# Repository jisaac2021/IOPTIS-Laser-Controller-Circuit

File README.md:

## IOPTIS NEW GEN Laser Controller Circuit

## **PCB Layout 3D View**

**Front**

**Back**

## **Multi-sheet Schematic Layout**

## **Team**
Julia Isaac - Machine Learning & Software Intern

Loic Billaut - Electrical & Optical Engineering Intern

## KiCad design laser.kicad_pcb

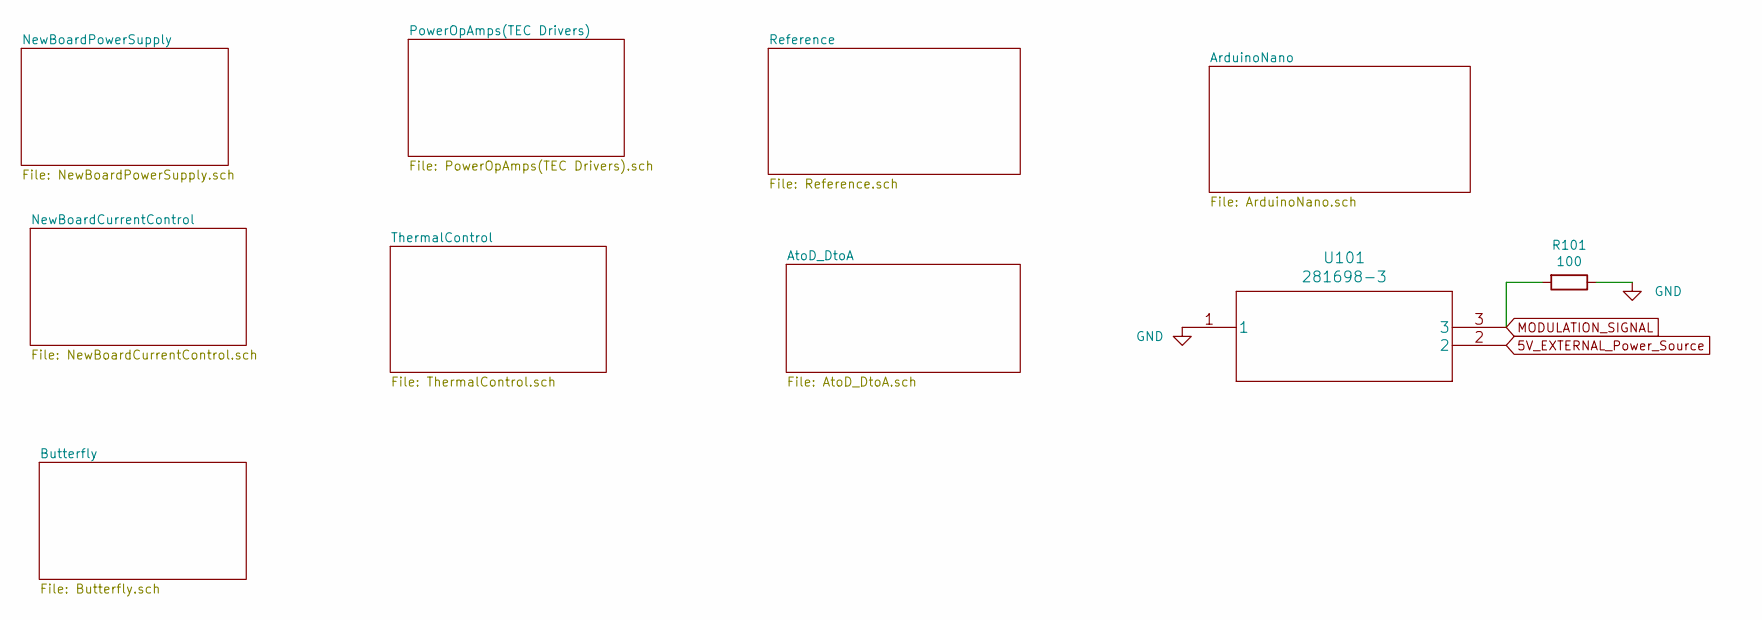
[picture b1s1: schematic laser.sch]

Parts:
R101: 100; R_0402_1005Metric
U101: 281698-3

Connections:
5V_EXTERNAL_Power_Source: U101.2; also elsewhere on the board
GND: R101.1, U101.1; also elsewhere on the board
MODULATION_SIGNAL: R101.2, U101.3; also elsewhere on the board

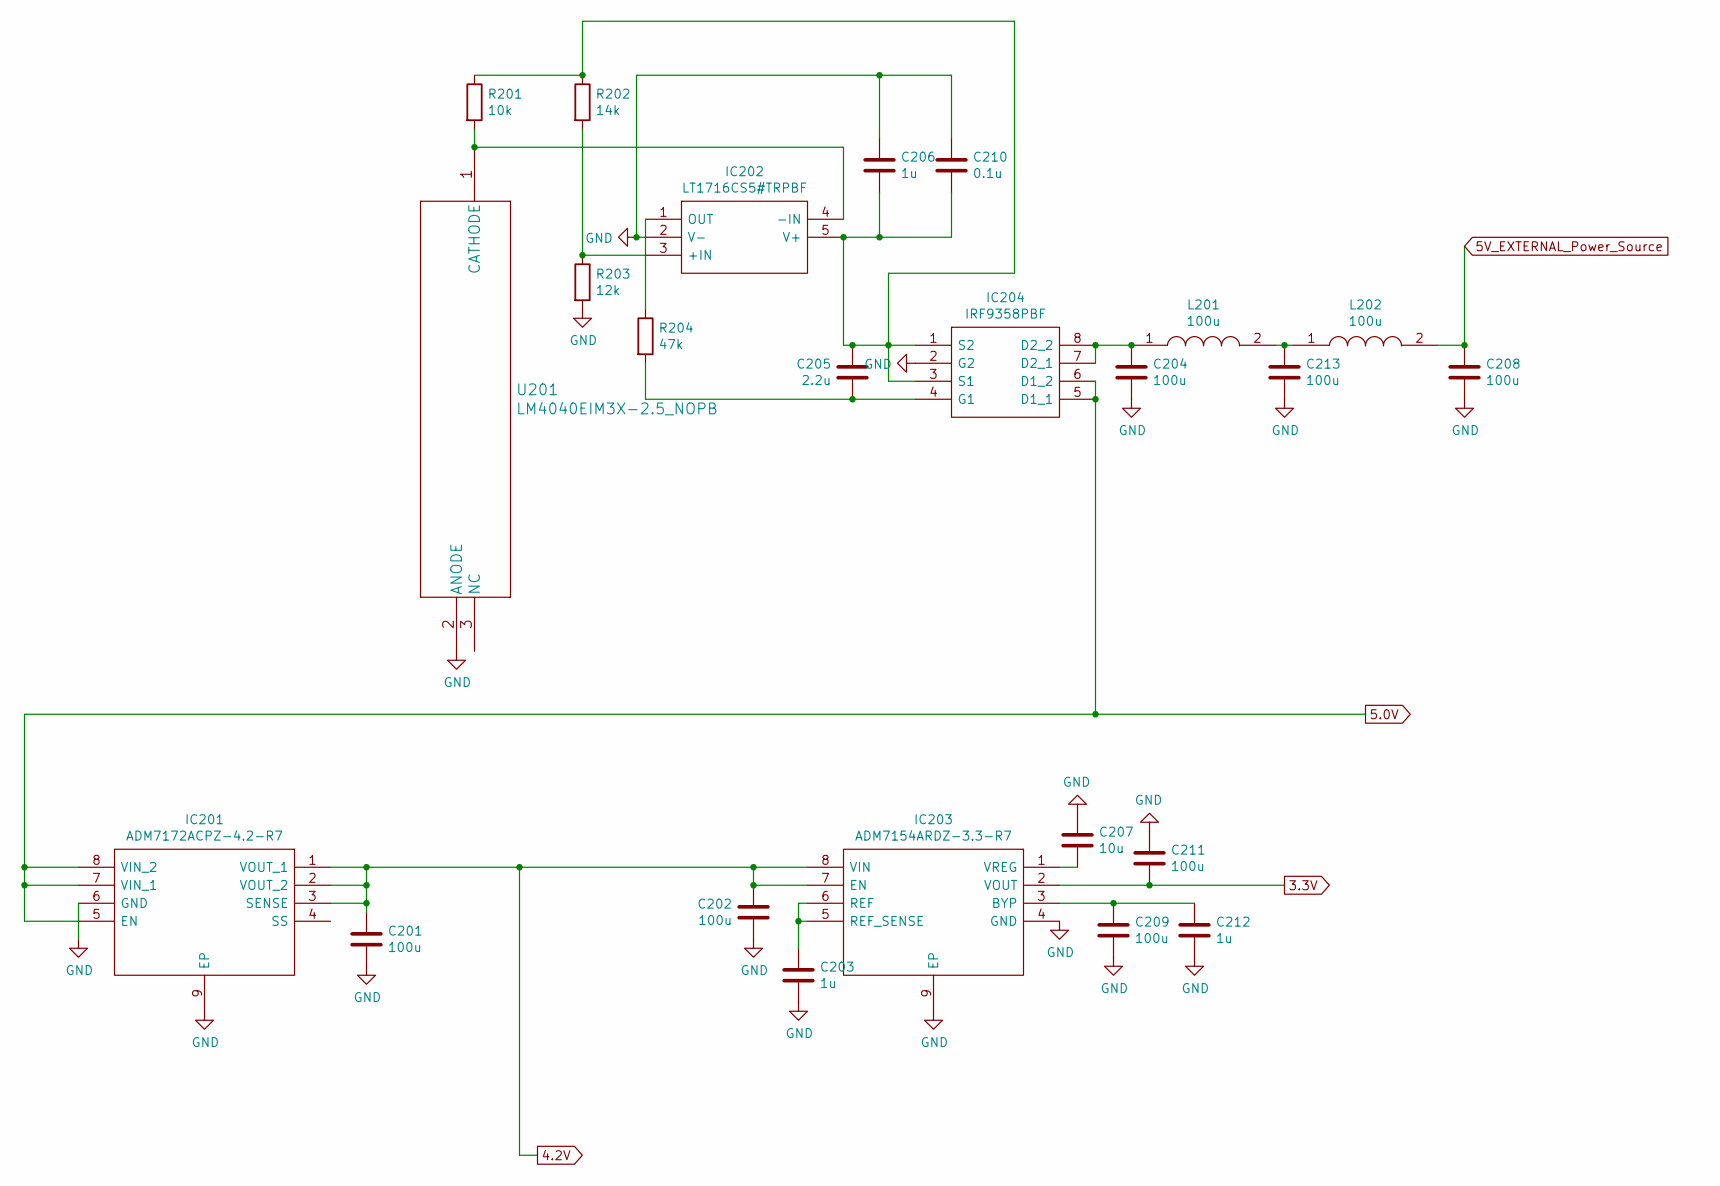
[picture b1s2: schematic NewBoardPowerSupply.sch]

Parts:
C201, C202, C204, C208, C209, C211, C213: 100u; C_1210_3225Metric
C203, C206, C212: 1u; C_0402_1005Metric
C205: 2.2u; C_0402_1005Metric
C207: 10u; C_0402_1005Metric
C210: 0.1u; C_0402_1005Metric
IC201: ADM7172ACPZ-4.2-R7; Manufacturer_Part_Number ADM7172ACPZ-4.2-R7; Mouser Part Number 584-ADM7172ACPZ4.2R7
IC202: LT1716CS5#TRPBF; Manufacturer_Part_Number LT1716CS5#TRPBF; Mouser Part Number 584-LT1716CS5#TRPBF
IC203: ADM7154ARDZ-3.3-R7; ADA4528-2ACPZ-RL; Manufacturer_Part_Number ADM7154ARDZ-3.3-R7; Mouser Part Number 584-ADM7154ARDZ3.3R7
IC204: IRF9358PBF; Manufacturer_Part_Number IRF9358PBF; Mouser Part Number 942-IRF9358PBF
L201, L202: 100u; 7447714220; Manufacturer_Part_Number 7447714101; Mouser Part Number 710-7447714101
R201: 10k; R_0402_1005Metric
R202: 14k; R_0805_2012Metric
R203: 12k; R_0402_1005Metric
R204: 47k; R_0402_1005Metric
U201: LM4040EIM3X-2.5_NOPB; LM4040EIM3X-2.5&slash_NOPB

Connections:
3.3V: C211.2, IC203.2 (VOUT); also elsewhere on the board
4.2V: C201.1, C202.1, IC201.1 (VOUT_1), IC201.2 (VOUT_2), IC201.3 (SENSE), IC203.7 (EN), IC203.8 (VIN); also elsewhere on the board
5.0V: IC201.5 (EN), IC201.7 (VIN_1), IC201.8 (VIN_2), IC204.5 (D1_1), IC204.6 (D1_2); also elsewhere on the board
5V_EXTERNAL_Power_Source: C208.2, L202.2; also elsewhere on the board
GND: C201.2, C202.2, C203.2, C204.1, C206.1, C207.1, C208.1, C209.2, C210.1, C211.1, C212.2, C213.1, IC201.6 (GND), IC201.9 (EP), IC202.2 (V-), IC203.4 (GND), IC203.9 (EP), IC204.2 (G2), R203.2, U201.2 (ANODE); also elsewhere on the board
unnamed: C203.1, IC203.5 (REF_SENSE), IC203.6 (REF)
unnamed: C204.2, IC204.7 (D2_1), IC204.8 (D2_2), L201.1
unnamed: C205.1, C206.2, C210.2, IC202.5 (V+), IC204.1 (S2), IC204.3 (S1), R201.1, R202.1
unnamed: C205.2, IC204.4 (G1), R204.2
unnamed: C207.2, IC203.1 (VREG)
unnamed: C209.1, C212.1, IC203.3 (BYP)
unnamed: C213.2, L201.2, L202.1
unnamed: IC202.1 (OUT), R204.1
unnamed: IC202.3 (+IN), R202.2, R203.1
unnamed: IC202.4 (-IN), R201.2, U201.1 (CATHODE)

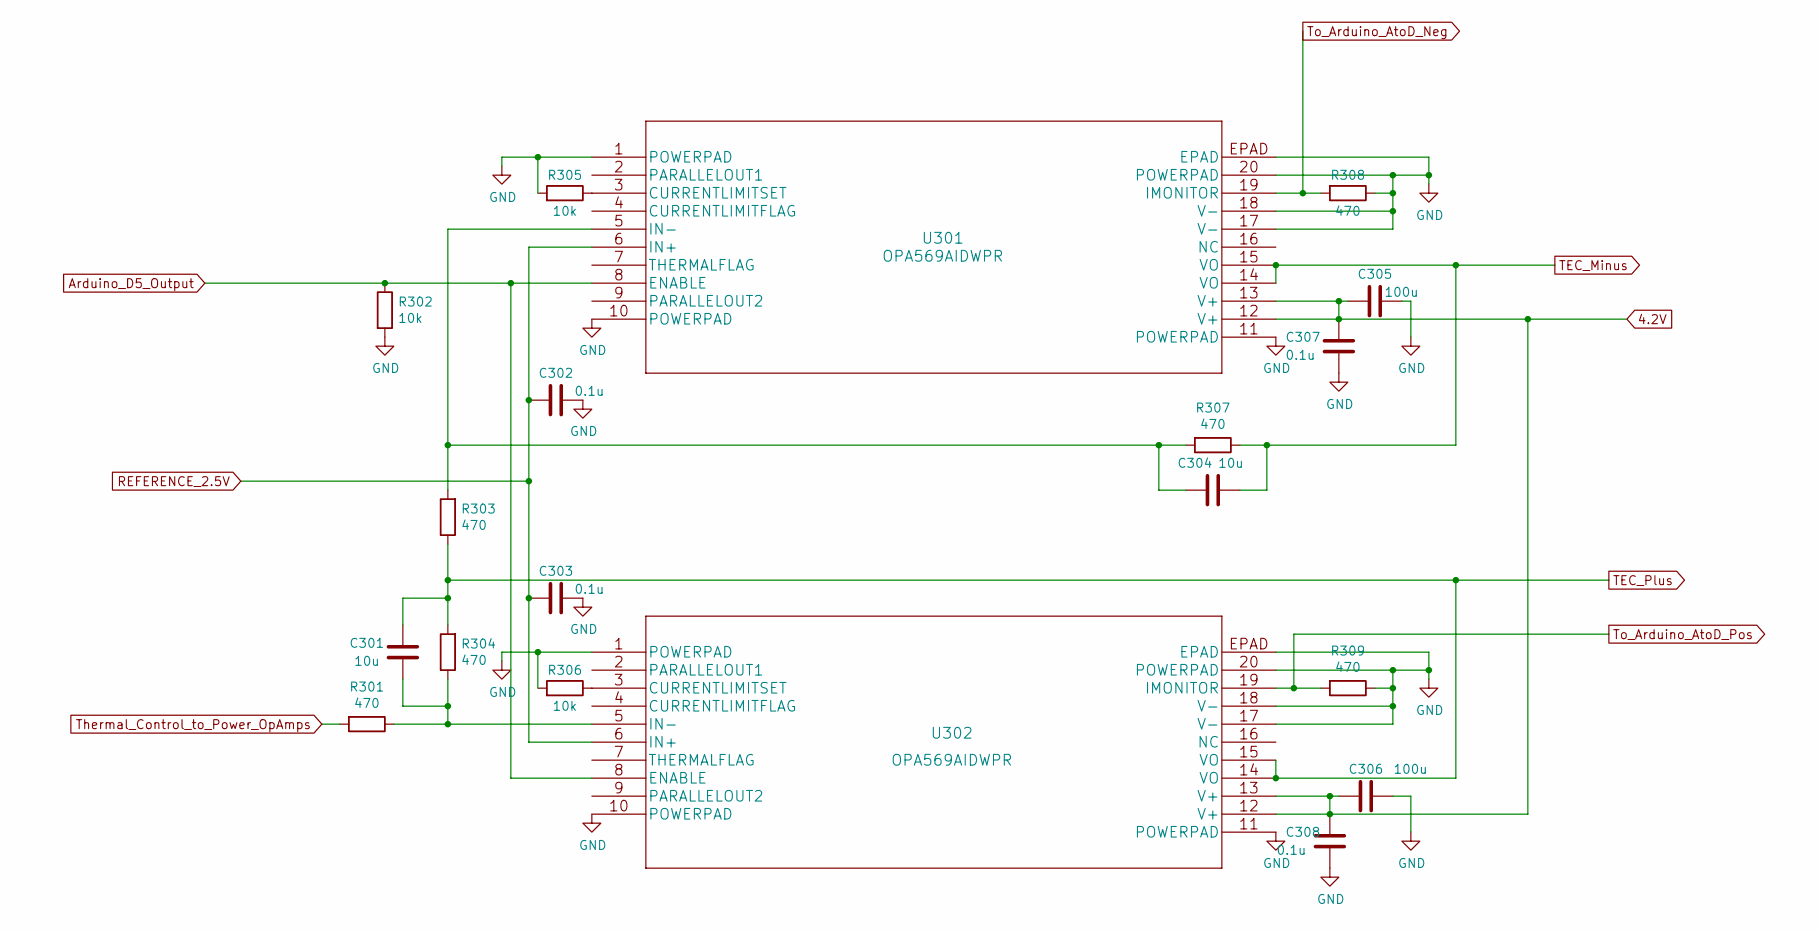
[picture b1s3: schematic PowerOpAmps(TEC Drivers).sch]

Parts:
C301, C304: 10u; C_0402_1005Metric
C302, C303, C307, C308: 0.1u; C_0402_1005Metric
C305, C306: 100u; C_1210_3225Metric
R301, R303, R304, R307, R308, R309: 470; R_0402_1005Metric
R302, R305, R306: 10k; R_0402_1005Metric
U301, U302: OPA569AIDWPR

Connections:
4.2V: C305.2, C306.2, C307.1, C308.1, U301.12 (V+), U301.13 (V+), U302.12 (V+), U302.13 (V+); also elsewhere on the board
Arduino_D5_Output: R302.1, U301.8 (ENABLE), U302.8 (ENABLE); also elsewhere on the board
GND: C302.1, C303.1, C305.1, C306.1, C307.2, C308.2, R302.2, R305.2, R306.2, R308.1, R309.1, U301.1 (POWERPAD), U301.10 (POWERPAD), U301.11 (POWERPAD), U301.17 (V-), U301.18 (V-), U301.20 (POWERPAD), U301.EPAD, U302.1 (POWERPAD), U302.10 (POWERPAD), U302.11 (POWERPAD), U302.17 (V-), U302.18 (V-), U302.20 (POWERPAD), U302.EPAD; also elsewhere on the board
unnamed: C301.1, R301.1, R304.1, U302.5 (IN-)
unnamed: C304.2, R303.2, R307.2, U301.5 (IN-)
unnamed: R305.1, U301.3 (CURRENTLIMITSET)
unnamed: R306.1, U302.3 (CURRENTLIMITSET)
REFERENCE_2.5V: C302.2, C303.2, U301.6 (IN+), U302.6 (IN+); also elsewhere on the board
TEC_Minus: C304.1, R307.1, U301.14 (VO), U301.15 (VO); also elsewhere on the board
TEC_Plus: C301.2, R303.1, R304.2, U302.14 (VO), U302.15 (VO); also elsewhere on the board
Thermal_Control_to_Power_OpAmps: R301.2; also elsewhere on the board
To_Arduino_AtoD_Neg: R308.2, U301.19 (IMONITOR); also elsewhere on the board
To_Arduino_AtoD_Pos: R309.2, U302.19 (IMONITOR); also elsewhere on the board

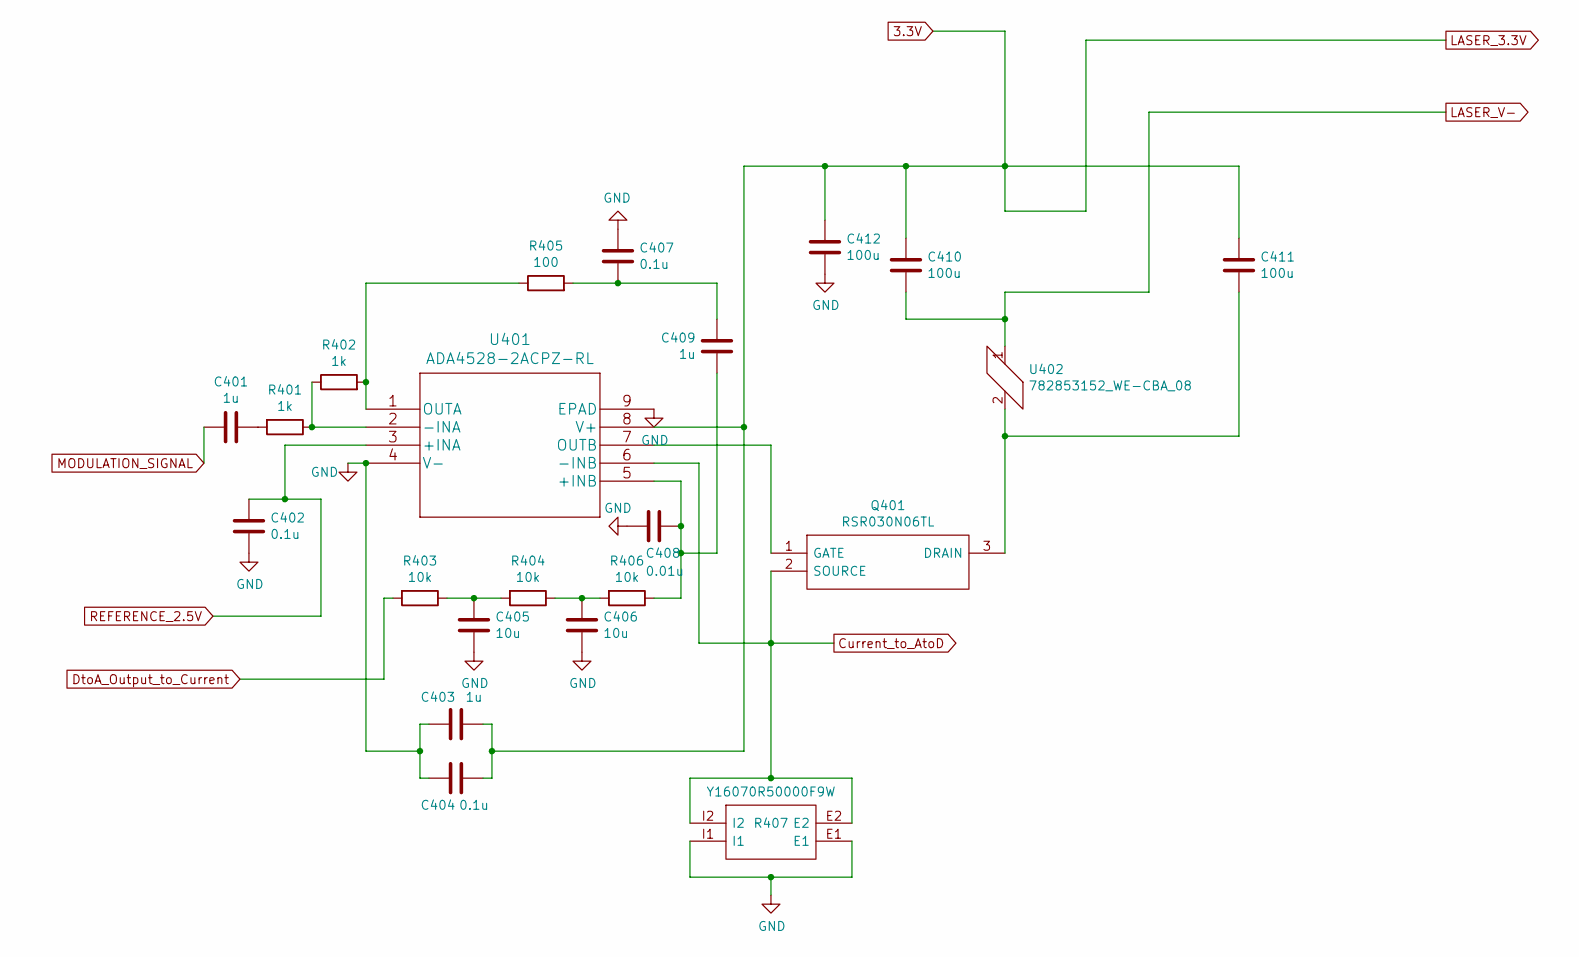
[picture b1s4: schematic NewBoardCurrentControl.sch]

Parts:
C401, C403, C409: 1u; C_0402_1005Metric
C402, C404, C407: 0.1u; C_0402_1005Metric
C405, C406: 10u; C_0402_1005Metric
C408: 0.01u; C_0402_1005Metric
C410, C411, C412: 100u; C_1210_3225Metric
Q401: RSR030N06TL; Manufacturer_Part_Number RSR030N06TL; Mouser Part Number 755-RSR030N06TL
R401, R402: 1k; R_0402_1005Metric
R403, R404, R406: 10k; R_0603_1608Metric
R405: 100; R_0402_1005Metric
R407: Y16070R50000F9W; Y16072R00000T9W; Manufacturer_Part_Number Y16070R50000F9W; Mouser Part Number 71-VCS1625Z0R5000FSW
U401: ADA4528-2ACPZ-RL
U402: 782853152_WE-CBA_08; 782853121

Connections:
3.3V: C403.1, C404.1, C410.1, C411.1, C412.1, U401.8 (V+); also elsewhere on the board
Current_to_AtoD: Q401.2 (SOURCE), R407.E2, R407.I2, U401.6 (-INB); also elsewhere on the board
DtoA_Output_to_Current: R403.2; also elsewhere on the board
GND: C402.1, C403.2, C404.2, C405.2, C406.2, C407.1, C408.2, C412.2, R407.E1, R407.I1, U401.4 (V-), U401.9 (EPAD); also elsewhere on the board
LASER_V-: C410.2, U402.1; also elsewhere on the board
MODULATION_SIGNAL: C401.2; also elsewhere on the board
unnamed: C401.1, R401.2
unnamed: C405.1, R403.1, R404.2
unnamed: C406.1, R404.1, R406.2
unnamed: C407.2, C409.1, R405.2
unnamed: C408.1, C409.2, R406.1, U401.5 (+INB)
unnamed: C411.2, Q401.3 (DRAIN), U402.2
unnamed: Q401.1 (GATE), U401.7 (OUTB)
unnamed: R401.1, R402.1, U401.2 (-INA)
unnamed: R402.2, R405.1, U401.1 (OUTA)
REFERENCE_2.5V: C402.2, U401.3 (+INA); also elsewhere on the board

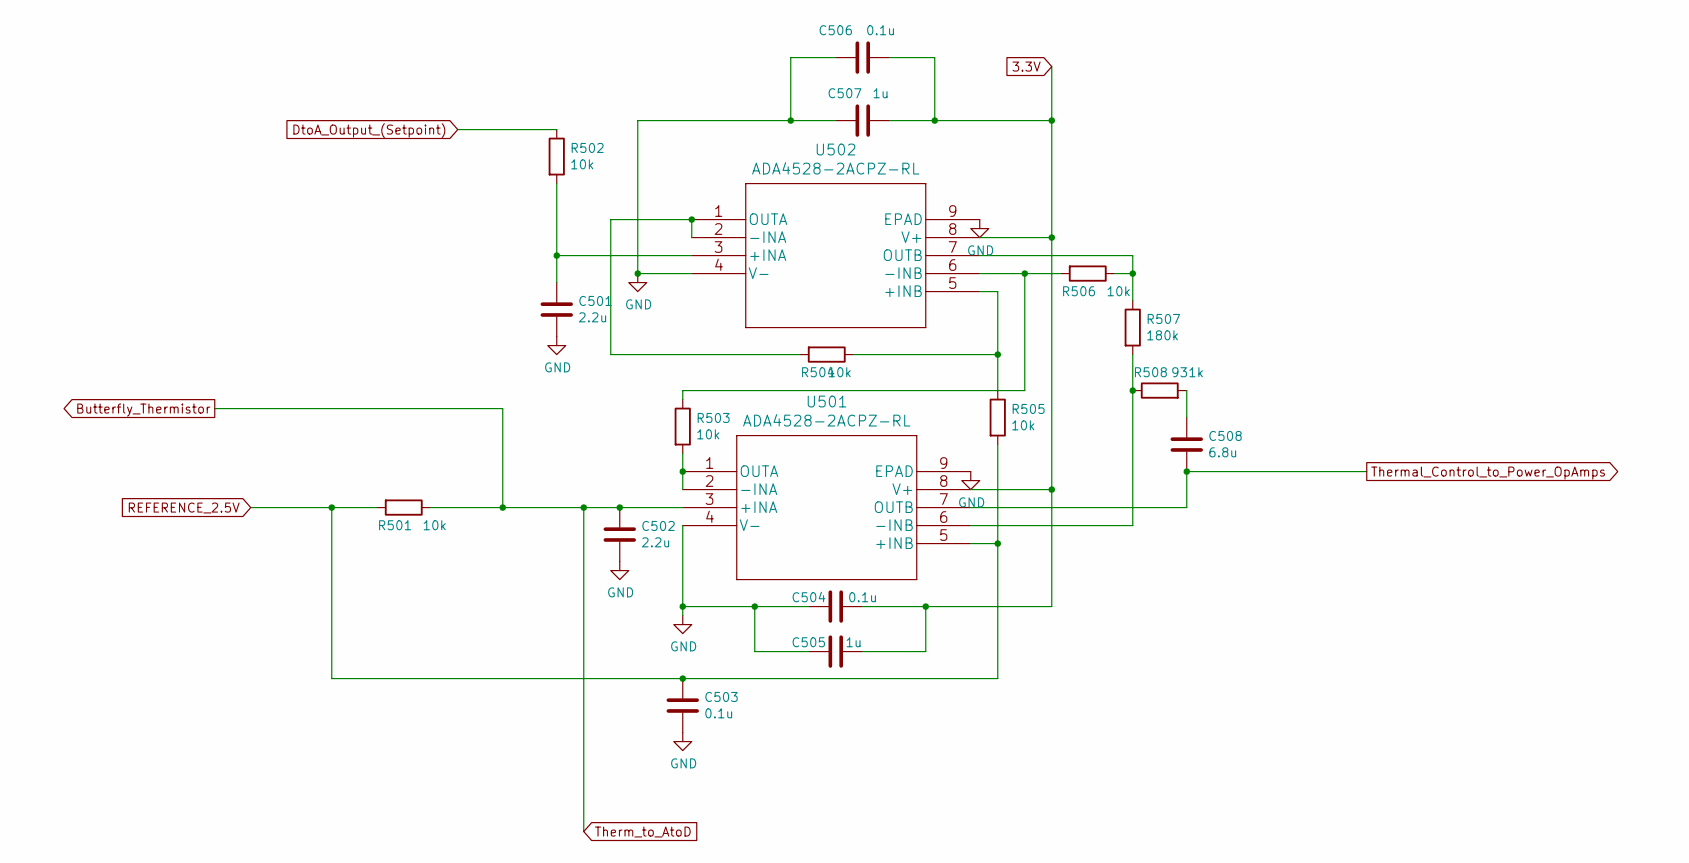
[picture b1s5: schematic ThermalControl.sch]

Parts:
C501, C502: 2.2u; C_0402_1005Metric
C503, C504, C506: 0.1u; C_0402_1005Metric
C505, C507: 1u; C_0402_1005Metric
C508: 6.8u; C_1812_4532Metric
R501, R502, R503, R504, R505, R506: 10k; R_0603_1608Metric
R507: 180k; R_0603_1608Metric
R508: 931k; R_0805_2012Metric
U501, U502: ADA4528-2ACPZ-RL

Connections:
3.3V: C504.1, C505.1, C506.1, C507.1, U501.8 (V+), U502.8 (V+); also elsewhere on the board
Butterfly_Thermistor: C502.1, R501.1, U501.3 (+INA); also elsewhere on the board
DtoA_Output_(Setpoint): R502.1; also elsewhere on the board
GND: C501.2, C502.2, C503.2, C504.2, C505.2, C506.2, C507.2, U501.4 (V-), U501.9 (EPAD), U502.4 (V-), U502.9 (EPAD); also elsewhere on the board
unnamed: C501.1, R502.2, U502.3 (+INA)
unnamed: C508.1, R508.2
unnamed: R503.1, R506.2, U502.6 (-INB)
unnamed: R503.2, U501.1 (OUTA), U501.2 (-INA)
unnamed: R504.1, R505.1, U502.5 (+INB)
unnamed: R504.2, U502.1 (OUTA), U502.2 (-INA)
unnamed: R506.1, R507.1, U502.7 (OUTB)
unnamed: R507.2, R508.1, U501.6 (-INB)
REFERENCE_2.5V: C503.1, R501.2, R505.2, U501.5 (+INB); also elsewhere on the board
Thermal_Control_to_Power_OpAmps: C508.2, U501.7 (OUTB); also elsewhere on the board

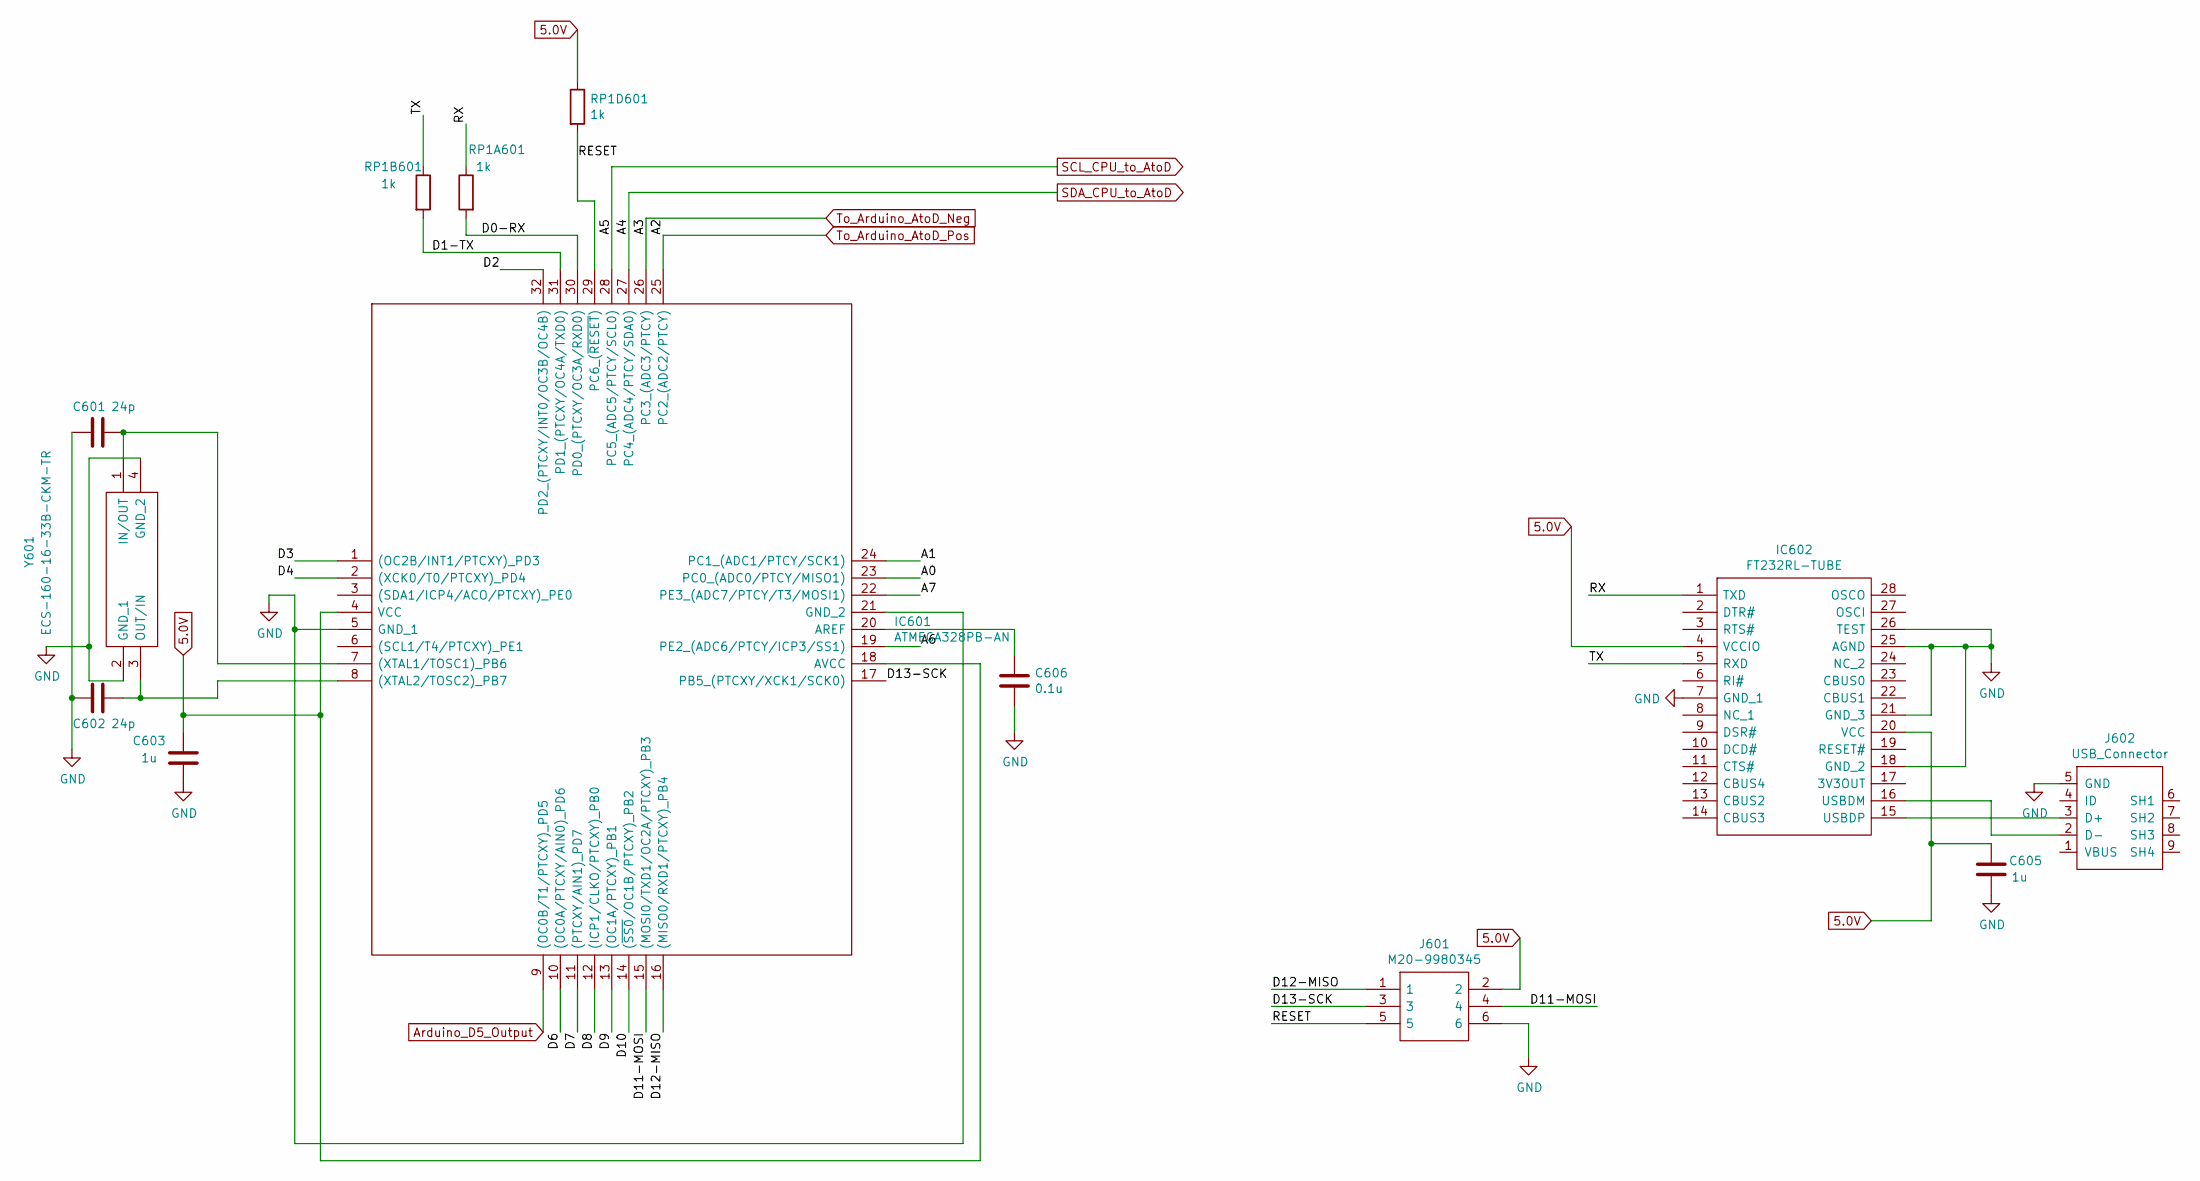
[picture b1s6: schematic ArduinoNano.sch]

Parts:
C601, C602: 24p; C_0402_1005Metric
C603, C605: 1u; C_0402_1005Metric
C606: 0.1u; C_0402_1005Metric
IC601: ATMEGA328PB-AN; QFP80P900X900X120-32N; Mouser Part Number 556-ATMEGA328PB-AN
IC602: FT232RL-TUBE; Manufacturer_Part_Number FT232RL-TUBE; Mouser Part Number 895-FT232RL-TUBE
J601: M20-9980345; Manufacturer_Part_Number M20-9980345; Mouser Part Number 855-M20-9980345
J602: USB_Connector; CUI_UJ2-MBH-1-SMT
RP1A601, RP1B601, RP1D601: 1k; R_0402_1005Metric
Y601: ECS-160-16-33B-CKM-TR; ECS1601633BCKMTR; Mouser Part Number 520-160-16-33B-CKMTR

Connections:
5.0V: C603.1, C605.1, IC601.4 (VCC), IC601.18 (AVCC), IC602.4 (VCCIO), IC602.20 (VCC), J601.2, RP1D601.1; also elsewhere on the board
/ArduinoNano/A0: IC601.23 (PC0_(ADC0/PTCY/MISO1))
/ArduinoNano/A1: IC601.24 (PC1_(ADC1/PTCY/SCK1))
/ArduinoNano/A6: IC601.19 (PE2_(ADC6/PTCY/ICP3/SS1))
/ArduinoNano/A7: IC601.22 (PE3_(ADC7/PTCY/T3/MOSI1))
/ArduinoNano/D0-RX: IC601.30 (PD0_(PTCXY/OC3A/RXD0)), RP1A601.2
/ArduinoNano/D1-TX: IC601.31 (PD1_(PTCXY/OC4A/TXD0)), RP1B601.2
/ArduinoNano/D2: IC601.32 (PD2_(PTCXY/INT0/OC3B/OC4B))
/ArduinoNano/D3: IC601.1 ((OC2B/INT1/PTCXY)_PD3)
/ArduinoNano/D4: IC601.2 ((XCK0/T0/PTCXY)_PD4)
/ArduinoNano/D6: IC601.10 ((OC0A/PTCXY/AIN0)_PD6)
/ArduinoNano/D7: IC601.11 ((PTCXY/AIN1)_PD7)
/ArduinoNano/D8: IC601.12 ((ICP1/CLKO/PTCXY)_PB0)
/ArduinoNano/D9: IC601.13 ((OC1A/PTCXY)_PB1)
/ArduinoNano/D10: IC601.14 ((~SS0~/OC1B/PTCXY)_PB2)
/ArduinoNano/D11-MOSI: IC601.15 ((MOSI0/TXD1/OC2A/PTCXY)_PB3), J601.4
/ArduinoNano/D12-MISO: IC601.16 ((MISO0/RXD1/PTCXY)_PB4), J601.1
/ArduinoNano/D13-SCK: IC601.17 (PB5_(PTCXY/XCK1/SCK0)), J601.3
/ArduinoNano/RESET: IC601.29 (PC6_(~RESET)), J601.5, RP1D601.2
/ArduinoNano/RX: IC602.1 (TXD), RP1A601.1
/ArduinoNano/TX: IC602.5 (RXD), RP1B601.1
Arduino_D5_Output: IC601.9 ((OC0B/T1/PTCXY)_PD5); also elsewhere on the board
GND: C601.2, C602.2, C603.2, C605.2, C606.2, IC601.5 (GND_1), IC601.21 (GND_2), IC602.7 (GND_1), IC602.18 (GND_2), IC602.21 (GND_3), IC602.25 (AGND), IC602.26 (TEST), J601.6, J602.5 (GND), Y601.2 (GND_1), Y601.4 (GND_2); also elsewhere on the board
unnamed: C601.1, IC601.7 ((XTAL1/TOSC1)_PB6), Y601.1 (IN/OUT)
unnamed: C602.1, IC601.8 ((XTAL2/TOSC2)_PB7), Y601.3 (OUT/IN)
unnamed: C606.1, IC601.20 (AREF)
unnamed: IC602.15 (USBDP), J602.3 (D+)
unnamed: IC602.16 (USBDM), J602.2 (D-)
SCL_CPU_to_AtoD: IC601.28 (PC5_(ADC5/PTCY/SCL0)); also elsewhere on the board
SDA_CPU_to_AtoD: IC601.27 (PC4_(ADC4/PTCY/SDA0)); also elsewhere on the board
To_Arduino_AtoD_Neg: IC601.26 (PC3_(ADC3/PTCY)); also elsewhere on the board
To_Arduino_AtoD_Pos: IC601.25 (PC2_(ADC2/PTCY)); also elsewhere on the board

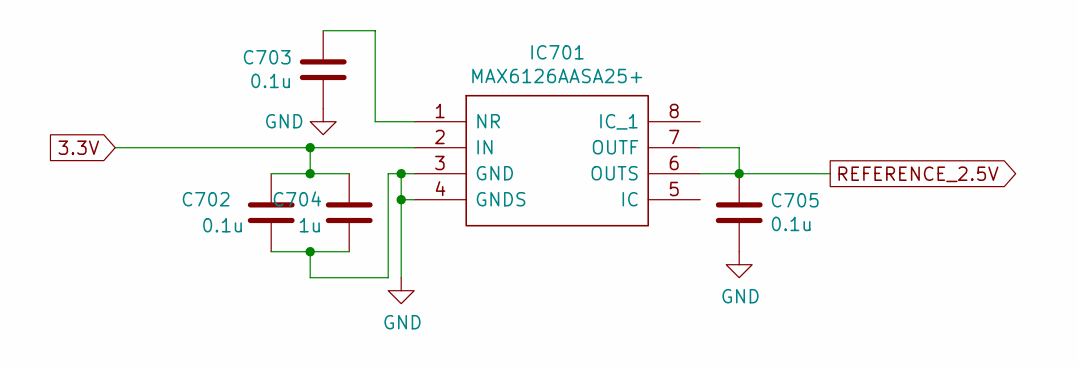
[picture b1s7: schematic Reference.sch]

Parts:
C702, C703, C705: 0.1u; C_0402_1005Metric
C704: 1u; C_0402_1005Metric
IC701: MAX6126AASA25+; MAX6126-25+; Manufacturer_Part_Number MAX6126AASA25+; Mouser Part Number 700-MAX6126AASA25

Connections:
3.3V: C702.1, C704.1, IC701.2 (IN); also elsewhere on the board
GND: C702.2, C703.2, C704.2, C705.2, IC701.3 (GND), IC701.4 (GNDS); also elsewhere on the board
unnamed: C703.1, IC701.1 (NR)
REFERENCE_2.5V: C705.1, IC701.6 (OUTS), IC701.7 (OUTF); also elsewhere on the board

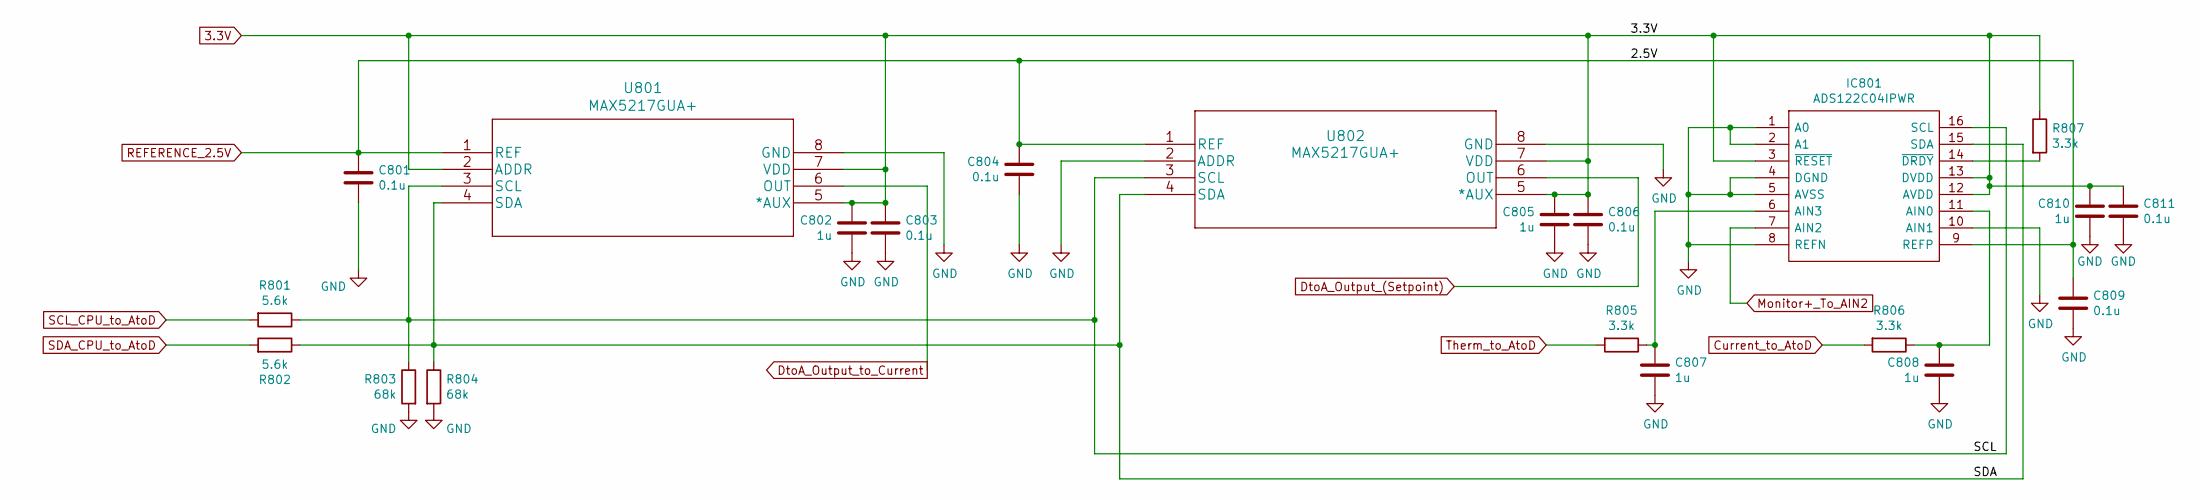
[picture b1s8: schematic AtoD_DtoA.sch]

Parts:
C801, C803, C804, C806, C809, C811: 0.1u; C_0402_1005Metric
C802, C805, C807, C808, C810: 1u; C_0402_1005Metric
IC801: ADS122C04IPWR; Manufacturer_Part_Number ADS122C04IPWR; Mouser Part Number 595-ADS122C04IPWR
R801, R802: 5.6k; R_0402_1005Metric
R803, R804: 68k; R_0402_1005Metric
R805, R806, R807: 3.3k; R_0402_1005Metric
U801, U802: MAX5217GUA+; MAX5217GUA&plus_

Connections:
3.3V: C802.1, C803.1, C805.1, C806.1, C810.1, C811.1, IC801.3 (~RESET), IC801.12 (AVDD), IC801.13 (DVDD), R807.1, U801.2 (ADDR), U801.5 (*AUX), U801.7 (VDD), U802.5 (*AUX), U802.7 (VDD); also elsewhere on the board
/AtoD_DtoA/SCL: IC801.16 (SCL), R801.1, R803.1, U801.3 (SCL), U802.3 (SCL)
/AtoD_DtoA/SDA: IC801.15 (SDA), R802.1, R804.1, U801.4 (SDA), U802.4 (SDA)
Butterfly_Thermistor: R805.2; also elsewhere on the board
Current_to_AtoD: R806.2; also elsewhere on the board
DtoA_Output_(Setpoint): U802.6 (OUT); also elsewhere on the board
DtoA_Output_to_Current: U801.6 (OUT); also elsewhere on the board
GND: C801.2, C802.2, C803.2, C804.2, C805.2, C806.2, C807.2, C808.2, C809.2, C810.2, C811.2, IC801.1 (A0), IC801.2 (A1), IC801.4 (DGND), IC801.5 (AVSS), IC801.8 (REFN), IC801.10 (AIN1), R803.2, R804.2, U801.8 (GND), U802.2 (ADDR), U802.8 (GND); also elsewhere on the board
Monitor+_To_AIN2: IC801.7 (AIN2); also elsewhere on the board
unnamed: C807.1, IC801.6 (AIN3), R805.1
unnamed: C808.1, IC801.11 (AIN0), R806.1
unnamed: IC801.14 (~DRDY), R807.2
REFERENCE_2.5V: C801.1, C804.1, C809.1, IC801.9 (REFP), U801.1 (REF), U802.1 (REF); also elsewhere on the board
SCL_CPU_to_AtoD: R801.2; also elsewhere on the board
SDA_CPU_to_AtoD: R802.2; also elsewhere on the board

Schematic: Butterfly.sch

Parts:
B1: butterfly; Butterfly
R901: 100k; R_0402_1005Metric

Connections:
3.3V: B1.11 (LDIODE2); also elsewhere on the board
Butterfly_Thermistor: B1.1 (THERM1); also elsewhere on the board
GND: B1.2 (THERM2), B1.5 (MDIODE2), B1.13 (LDIODE3), B1.14, R901.2; also elsewhere on the board
LASER_V-: B1.3 (LDIODE1); also elsewhere on the board
Monitor+_To_AIN2: B1.4 (MDIODE1), R901.1; also elsewhere on the board
TEC_Minus: B1.7 (TEC-); also elsewhere on the board
TEC_Plus: B1.6 (TEC+); also elsewhere on the board

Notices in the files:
laser.kicad_pcb:
Copyright ©
parts and their libraries:
Copyright 2021 Accelerated Designs. All rights reserved.
